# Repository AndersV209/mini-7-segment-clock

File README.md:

# mini-7-segment-clock
upload of an old project i made a couple of years ago. 

there are a couple of pictures of how the pcb files are connected to make a clock, and how the RTC is added. 

if you have any questions plzz ask and i will try to answer them. 

it is called mini because it is a mini version of another 7 segment clock i have made years before this one was made.

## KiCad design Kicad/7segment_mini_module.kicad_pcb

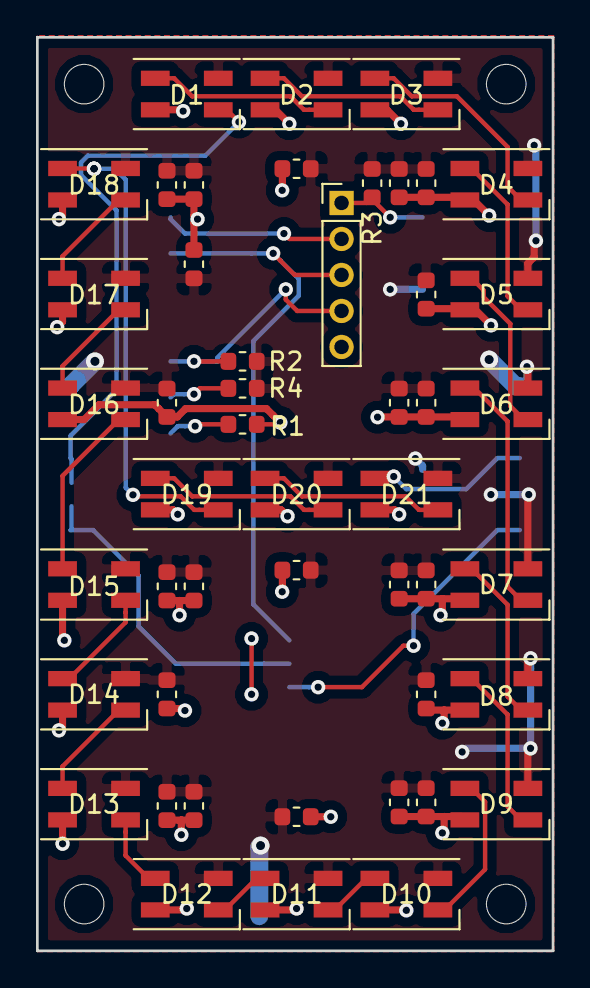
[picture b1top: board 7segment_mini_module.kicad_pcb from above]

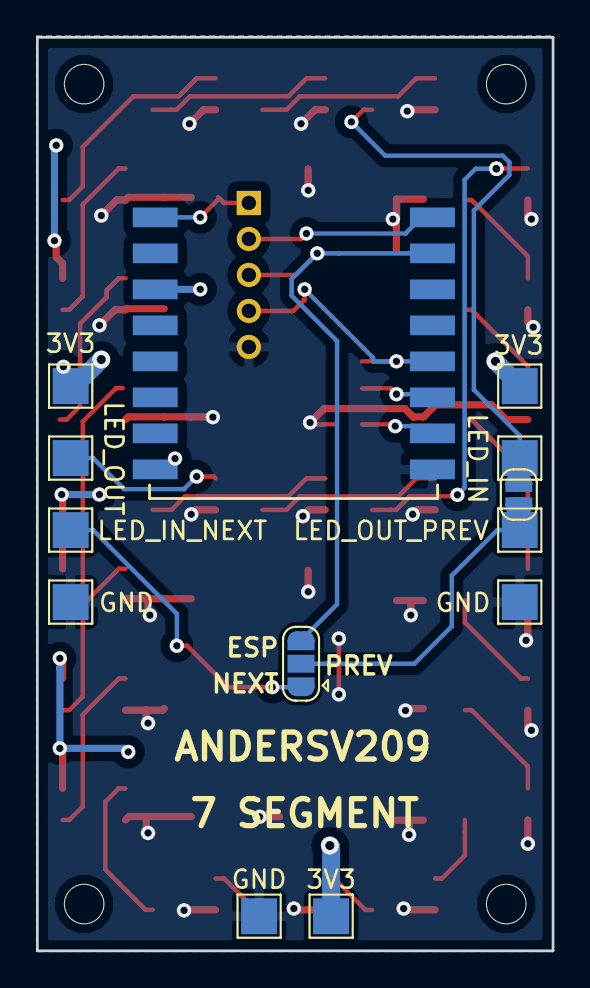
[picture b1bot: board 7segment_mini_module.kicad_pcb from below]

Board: 2 copper layers, 28.7 x 50.8 mm, 65 parts (13 on the bottom side), 32 nets.

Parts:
C1, C2, C3, C4, C5, C6, C7, C8, C9, C10, C11, C12, C13, C14, C15, C16, C17, C18, C19, C20, C21, C22: 100nF; C_0603_1608Metric
D1, D2, D3, D4, D5, D6, D7, D8, D9, D10, D11, D12, D13, D14, D15, D16, D17, D18, D19, D20, D21: SK6812MINI; LED_SK6812MINI_PLCC4_3.5x3.5mm_P1.75mm
H1, H2, H3, H4: MountingHole; MountingHole_2.2mm_M2
J1: Conn_01x05; PinHeader_1x05_P2.00mm_Vertical
JP1: SolderJumper_3_Open; SolderJumper-3_P1.3mm_Open_RoundedPad1.0x1.5mm
JP2: SolderJumper_2_Open; SolderJumper-2_P1.3mm_Open_RoundedPad1.0x1.5mm
R1, R2, R3, R4: 10K; R_0603_1608Metric
TP1, TP2, TP9: 3V3; TestPoint_Pad_2.0x2.0mm
TP3: LED_IN; TestPoint_Pad_2.0x2.0mm
TP4: LED_OUT; TestPoint_Pad_2.0x2.0mm
TP5: LED_OUT_PREV; TestPoint_Pad_2.0x2.0mm
TP6: LED_IN_NEXT; TestPoint_Pad_2.0x2.0mm
TP7, TP8, TP10: GND; TestPoint_Pad_2.0x2.0mm
U1: ESP-12; ESP-12_SMD

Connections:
+3V3: C1.1, C2.1, C3.1, C4.1, C5.1, C6.1, C7.1, C8.1, C9.1, C10.1, C11.1, C12.1, C13.1, C14.1, C15.1, C16.1, C17.1, C18.1, C19.1, C20.1, C21.1, C22.1, D1.4, D2.4, D3.4, D4.4, D5.4, D6.4, D7.4, D8.4, D9.4, D10.4, D11.4, D12.4, D13.4, D14.4, D15.4, D16.4, D17.4, D18.4, D19.4, D20.4, D21.4, R1.1, R2.1, R3.1, TP1.1, TP2.1, TP9.1, U1.3, U1.8
ESP_LED: J1.3, JP1.3, U1.15
GND: C1.2, C2.2, C3.2, C4.2, C5.2, C6.2, C7.2, C8.2, C9.2, C10.2, C11.2, C12.2, C13.2, C14.2, C15.2, C16.2, C17.2, C18.2, C19.2, C20.2, C21.2, C22.2, D1.2, D2.2, D3.2, D4.2, D5.2, D6.2, D7.2, D8.2, D9.2, D10.2, D11.2, D12.2, D13.2, D14.2, D15.2, D16.2, D17.2, D18.2, D19.2, D20.2, D21.2, J1.5, R4.2, TP7.1, TP8.1, TP10.1, U1.9
GPIO0: J1.4, R2.2, U1.12
GPIO2: R1.2, U1.11
GPIO15: R4.1, U1.10
LED_IN: D1.3, JP2.1, TP3.1
LED_IN_NEXT: JP1.1, TP6.1
LED_OUT: D21.1, TP4.1
LED_OUT_Prev: JP1.2, JP2.2, TP5.1
unnamed: D1.1, D2.3
unnamed: D2.1, D3.3
unnamed: D3.1, D4.3
unnamed: D4.1, D5.3
unnamed: D5.1, D6.3
unnamed: D6.1, D7.3
unnamed: D7.1, D8.3
unnamed: D8.1, D9.3
unnamed: D10.1, D11.3
unnamed: D9.1, D10.3
unnamed: D11.1, D12.3
unnamed: D12.1, D13.3
unnamed: D13.1, D14.3
unnamed: D14.1, D15.3
unnamed: D15.1, D16.3
unnamed: D16.1, D17.3
unnamed: D17.1, D18.3
unnamed: D18.1, D19.3
unnamed: D19.1, D20.3
unnamed: D20.1, D21.3
RESET: J1.1, R3.2, U1.1
TX: J1.2, U1.16

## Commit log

2025-01-24 add stl files
2025-01-24 add software example and update readme
